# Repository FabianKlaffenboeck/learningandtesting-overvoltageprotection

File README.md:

# OverVoltageProtection

# My first PCB with automatic image generation

### Images

### Animation

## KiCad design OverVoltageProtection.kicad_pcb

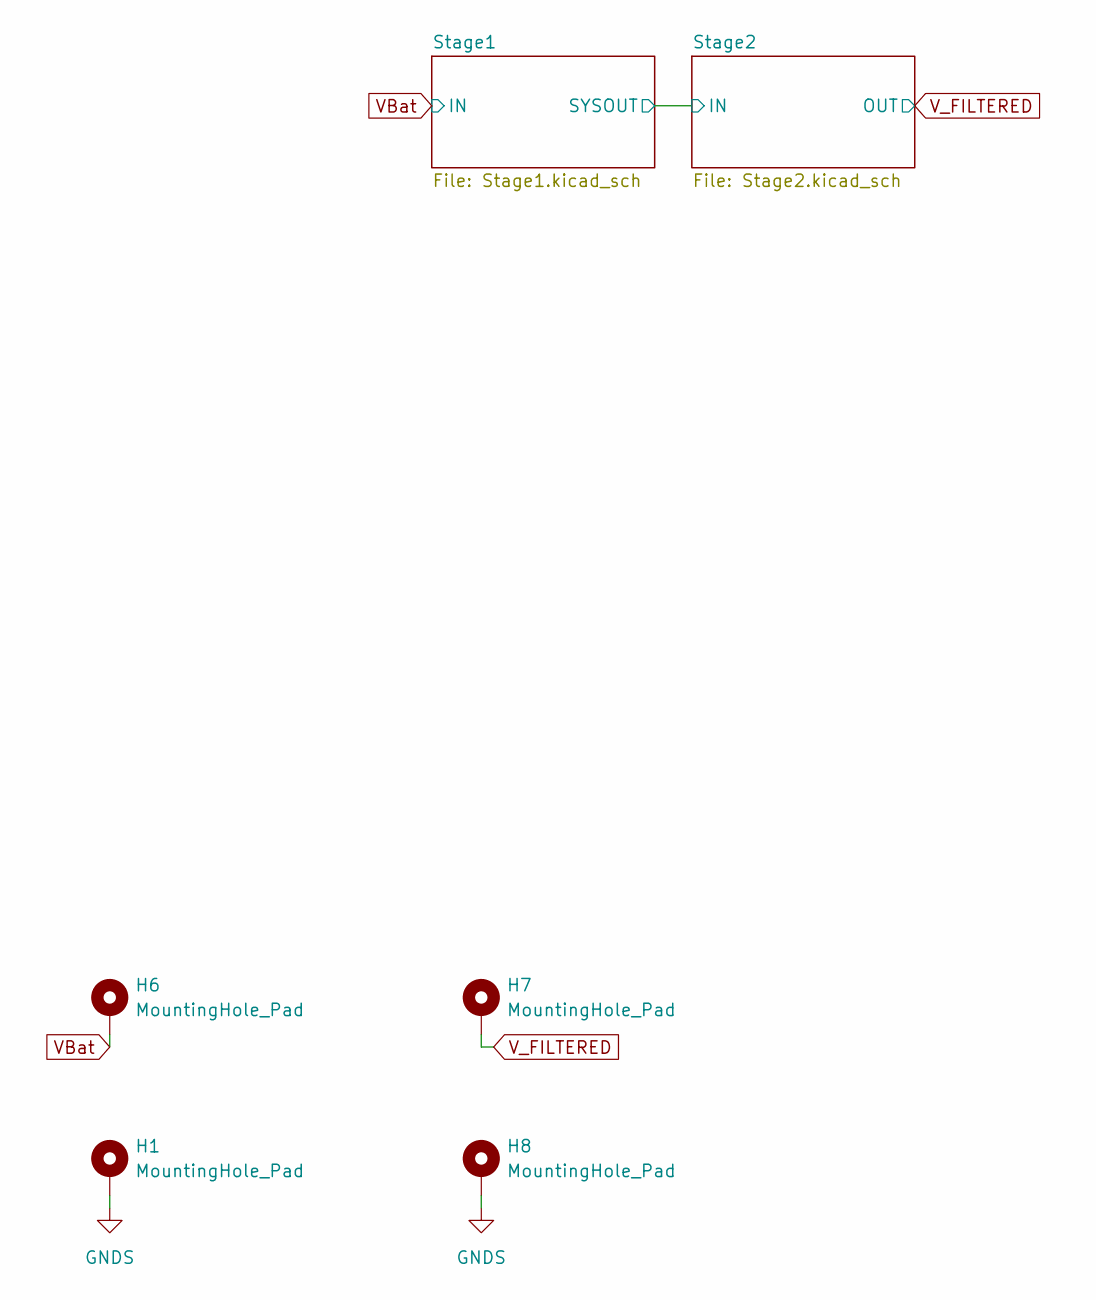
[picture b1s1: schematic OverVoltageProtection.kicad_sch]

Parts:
H1, H6, H7, H8: MountingHole_Pad; MountingHole_3.2mm_M3_Pad

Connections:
GNDS: H1.1, H8.1; also elsewhere on the board
VBat: H6.1; also elsewhere on the board
V_FILTERED: H7.1; also elsewhere on the board

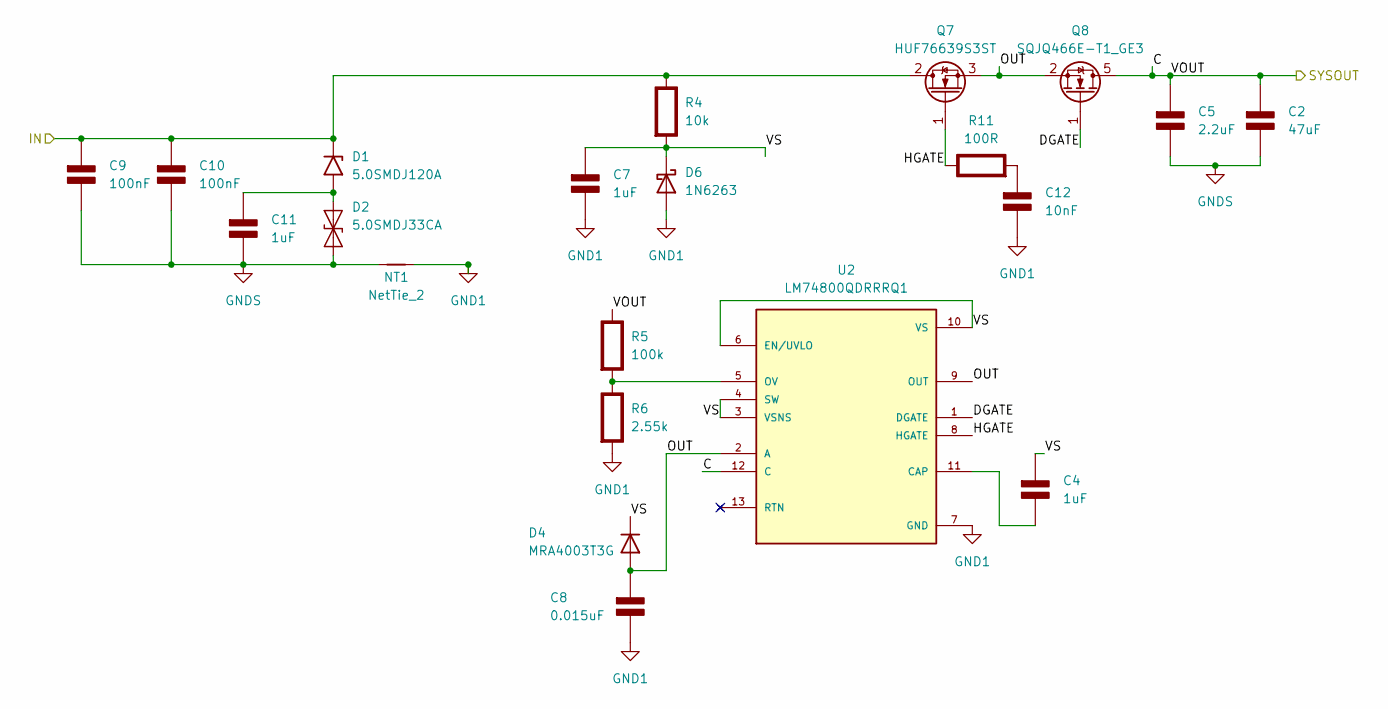
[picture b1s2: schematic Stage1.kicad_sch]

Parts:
C2: 47uF; CP_Elec_8x10; Rating V
C4, C7, C11: 1uF; C_1206_3216Metric; Rating V
C5: 2.2uF; C_0805_2012Metric; Rating V
C8: 0.015uF; C_1206_3216Metric; Rating V
C9, C10: 100nF; C_0805_2012Metric; Rating V
C12: 10nF; C_0805_2012Metric; Rating V
D1: 5.0SMDJ120A; D_SMC
D2: 5.0SMDJ33CA; D_SMC
D4: MRA4003T3G; D_SMA
D6: 1N6263; D_SOD-123
NT1: NetTie_2; NetTie-2_SMD_Pad0.5mm
Q7: HUF76639S3ST; TO-263-3_TabPin2
Q8: SQJQ466E-T1_GE3; LFPAK88
R4: 10k; R_1206_3216Metric; Rating W
R5: 100k; R_1206_3216Metric; Rating W
R6: 2.55k; R_1206_3216Metric; Rating W
R11: 100R; R_1206_3216Metric_Pad1.30x1.75mm_HandSolder; Rating W
U2: LM74800QDRRRQ1; IC_LM74800QDRRRQ1; PARTREV C

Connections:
/Stage1/C: C2.1 (+), C5.1 (+), Q8.5 (D), R5.1 (+), U2.12 (C); also elsewhere on the board
/Stage1/DGATE: Q8.1 (G), U2.1 (DGATE)
/Stage1/HGATE: Q7.1 (G), R11.1 (+), U2.8 (HGATE)
/Stage1/OUT: C8.1 (+), D4.2 (A), Q7.3 (S), Q8.2 (S), Q8.3 (S), Q8.4 (S), U2.2 (A), U2.9 (OUT)
/Stage1/VS: C4.1 (+), C7.1 (+), D4.1 (K), D6.1 (K), R4.2 (-), U2.3 (VSNS), U2.4 (SW), U2.6 (EN/UVLO), U2.10 (VS)
GND1: C7.2 (-), C8.2 (-), C12.2 (-), D6.2 (A), NT1.1, R6.2 (-), U2.7 (GND)
GNDS: C2.2 (-), C5.2 (-), C9.2 (-), C10.2 (-), C11.2 (-), D2.1 (A1), NT1.2; also elsewhere on the board
unnamed: C4.2 (-), U2.11 (CAP)
unnamed: C11.1 (+), D1.2 (A2), D2.2 (A2)
unnamed: C12.1 (+), R11.2 (-)
unnamed: R5.2 (-), R6.1 (+), U2.5 (OV)
VBat: C9.1 (+), C10.1 (+), D1.1 (A1), Q7.2 (D), R4.1 (+); also elsewhere on the board

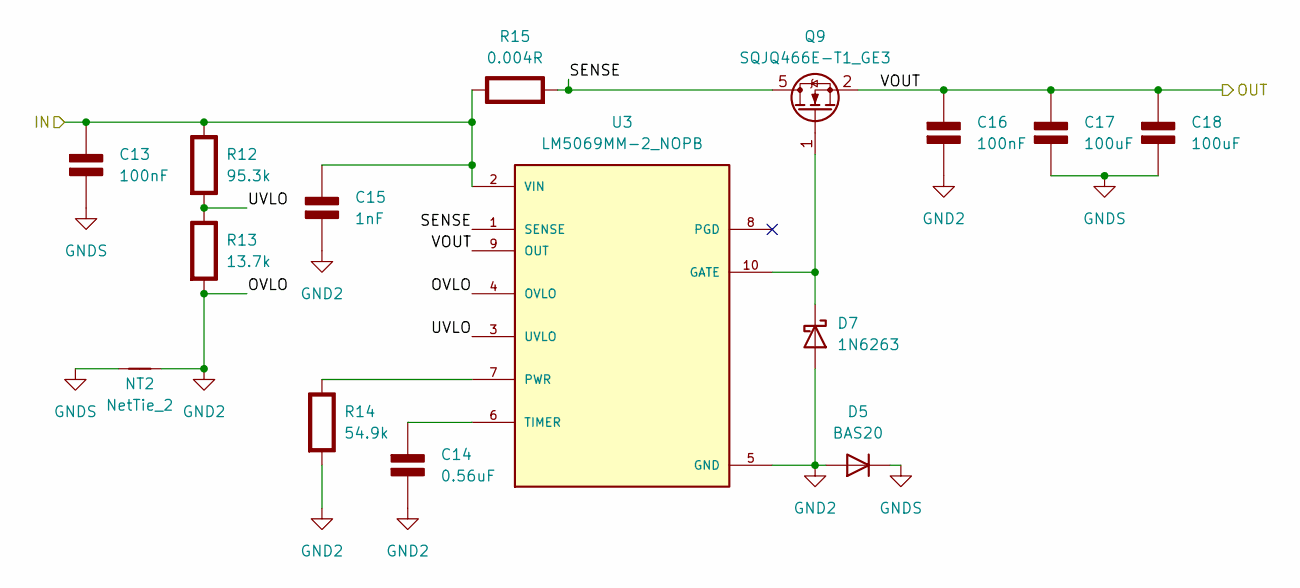
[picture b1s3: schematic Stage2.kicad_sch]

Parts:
C13, C16: 100nF; C_0805_2012Metric; Rating V
C14: 0.56uF; C_1206_3216Metric; Rating V
C15: 1nF; C_0603_1608Metric; Rating V
C17, C18: 100uF; CP_Elec_8x10; Rating V
D5: BAS20; SOT-23
D7: 1N6263; D_SOD-123
NT2: NetTie_2; NetTie-2_SMD_Pad0.5mm
Q9: SQJQ466E-T1_GE3; LFPAK88
R12: 95.3k; R_1206_3216Metric; Rating W
R13: 13.7k; R_1206_3216Metric; Rating W
R14: 54.9k; R_1206_3216Metric; Rating W
R15: 0.004R; R_Shunt_Vishay_WSR2_WSR3_KelvinConnection; Rating W
U3: LM5069MM-2_NOPB; SOP50P490X110-10N; PARTREV G

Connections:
/Stage1/C: C13.1 (+), C15.1 (+), R12.1 (+), R15.1 (+), U3.2 (VIN); also elsewhere on the board
/Stage2/SENSE: Q9.5 (D), R15.2 (-), U3.1 (SENSE)
/Stage2/UVLO: R12.2 (-), R13.1 (+), U3.3 (UVLO)
GND2: C14.2 (-), C15.2 (-), C16.2 (-), D5.1 (A), D7.2 (A), NT2.2, R13.2 (-), R14.2 (-), U3.4 (OVLO), U3.5 (GND)
GNDS: C13.2 (-), C17.2 (-), C18.2 (-), D5.3 (K), NT2.1; also elsewhere on the board
unnamed: C14.1 (+), U3.6 (TIMER)
unnamed: D7.1 (K), Q9.1 (G), U3.10 (GATE)
unnamed: R14.1 (+), U3.7 (PWR)
V_FILTERED: C16.1 (+), C17.1 (+), C18.1 (+), Q9.2 (S), Q9.3 (S), Q9.4 (S), U3.9 (OUT); also elsewhere on the board

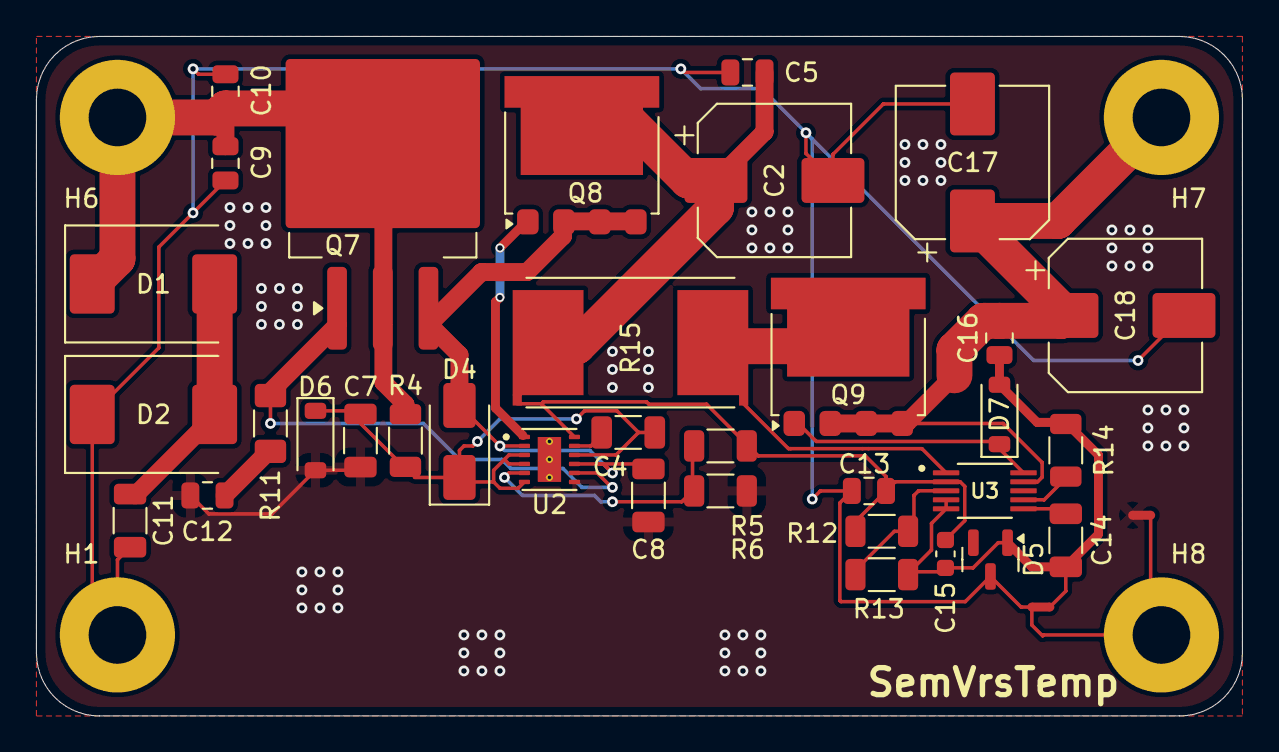
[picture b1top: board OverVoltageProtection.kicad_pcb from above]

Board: 2 copper layers, 67.0 x 37.8 mm, 40 parts (0 on the bottom side), 19 nets.

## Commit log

2024-10-27 added ci files
2024-10-28 first protection
2024-10-28 sample layout
2024-11-02 prototyple schematics finished
2024-11-02 added some docs
2025-01-12 completed schematics
2025-01-12 added palceholder
2025-01-26 finished layout
2025-01-26 bugfix
2025-01-28 error fixing
2025-01-28 bug fixing
2025-01-28 added readme
2025-03-23 Reworked schematics
2025-03-24 new layout
2025-03-24 updated kibot version
2025-03-24 fixed drc
2025-03-24 updated trace with
2025-03-25 smal changes
2025-03-25 added via patches
2025-04-02 change mosfet name
2025-04-11 fixed HW bug ?
2025-04-14 updated layout
2025-04-16 Add new file
